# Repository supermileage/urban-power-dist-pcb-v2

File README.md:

# urban-power-dist-pcb-v2

Meet *Shuriken*! Replacement for the old urban low power distribution PCB, [*Spidey*](https://github.com/supermileage/urban-power-dist-pcb).

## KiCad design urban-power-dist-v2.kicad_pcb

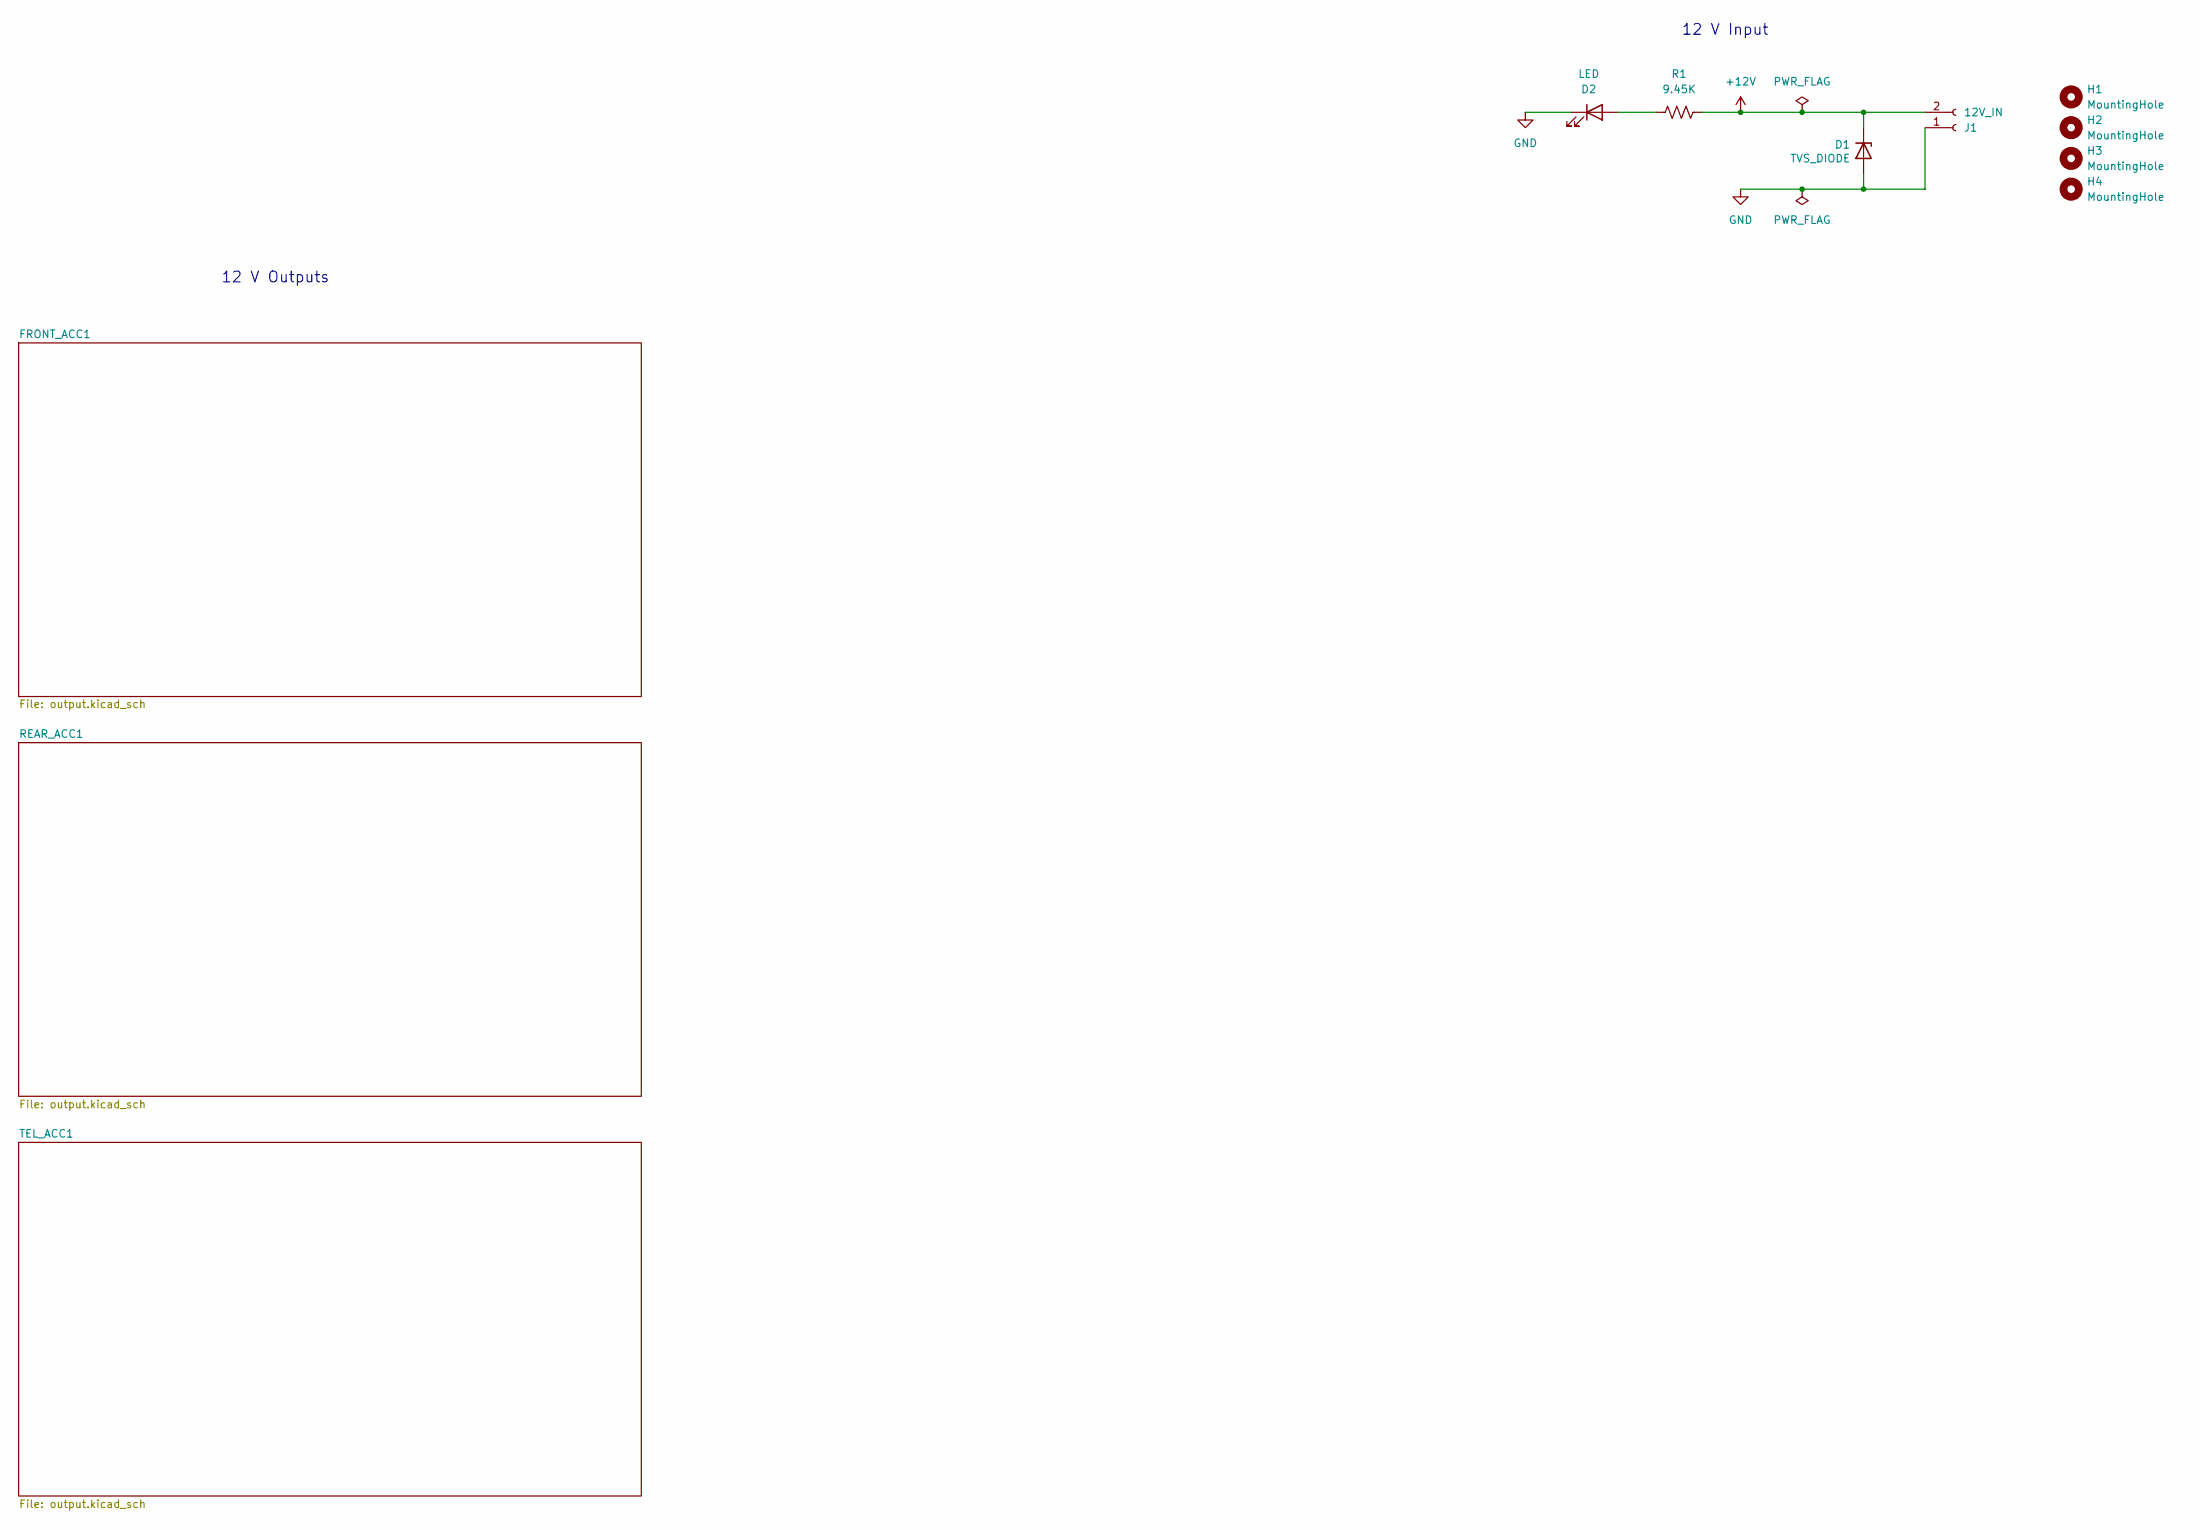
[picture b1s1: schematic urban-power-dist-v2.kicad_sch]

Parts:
D1: TVS_DIODE; D_SMF
D2: LED; LED_0603_1608Metric_Pad1.05x0.95mm_HandSolder
H1, H2, H3, H4: MountingHole; MountingHole_3.2mm_M3
J1: 12V_IN; ATF132PBM03
R1: 9.45K; R_1206_3216Metric_Pad1.30x1.75mm_HandSolder

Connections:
+12V: D1.1 (K), J1.2, R1.1; also elsewhere on the board
GND: D1.2 (A), D2.1 (K), J1.1; also elsewhere on the board
unnamed: D2.2 (A), R1.2

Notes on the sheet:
12 V Outputs
12 V Input

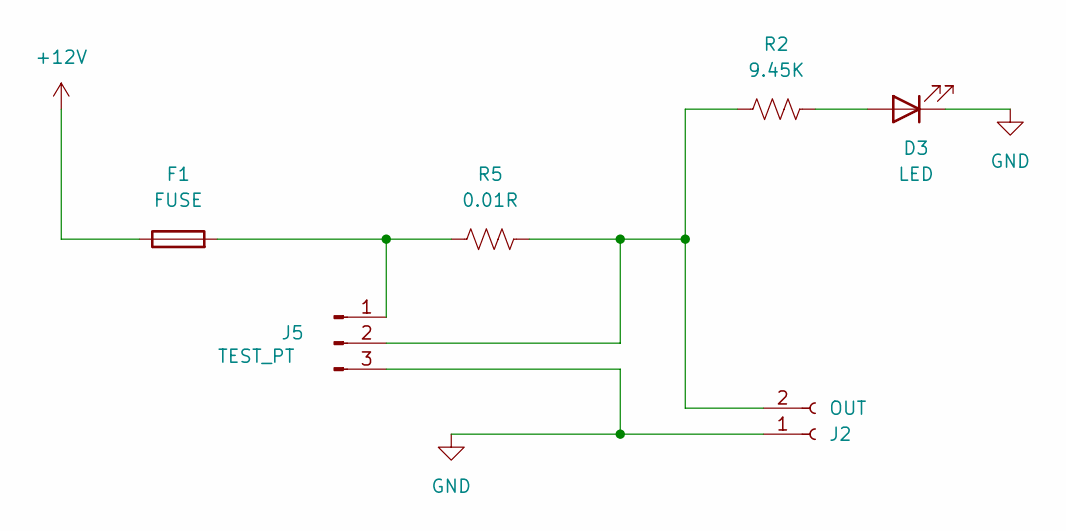
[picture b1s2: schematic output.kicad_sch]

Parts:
D3: LED; LED_0603_1608Metric_Pad1.05x0.95mm_HandSolder
F1: FUSE; Fuseholder_Blade_Mini_Keystone_3568
J2: OUT; ATF132PBM03
J5: TEST_PT; PinHeader_1x03_P2.54mm_Vertical
R2: 9.45K; R_1206_3216Metric_Pad1.30x1.75mm_HandSolder
R5: 0.01R; R_0805_2012Metric_Pad1.20x1.40mm_HandSolder

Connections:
+12V: F1.1; also elsewhere on the board
GND: D3.1 (K), J2.1, J5.3; also elsewhere on the board
unnamed: D3.2 (A), R2.1
unnamed: J2.2, J5.2, R2.2, R5.2
unnamed: F1.2, J5.1, R5.1

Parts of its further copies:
D4, D5: LED; LED_0603_1608Metric_Pad1.05x0.95mm_HandSolder
F2, F3: FUSE; Fuseholder_Blade_Mini_Keystone_3568
J3, J4: OUT; ATF132PBM03
J6, J7: TEST_PT; PinHeader_1x03_P2.54mm_Vertical
R3, R4: 9.45K; R_1206_3216Metric_Pad1.30x1.75mm_HandSolder
R6, R7: 0.01R; R_0805_2012Metric_Pad1.20x1.40mm_HandSolder

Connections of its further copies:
+12V: F2.1, F3.1; also elsewhere on the board
GND: D4.1 (K), D5.1 (K), J3.1, J4.1, J6.3, J7.3; also elsewhere on the board
unnamed: D4.2 (A), R3.1
unnamed: D5.2 (A), R4.1
unnamed: J3.2, J6.2, R3.2, R6.2
unnamed: J4.2, J7.2, R4.2, R7.2
unnamed: F2.2, J6.1, R6.1
unnamed: F3.2, J7.1, R7.1

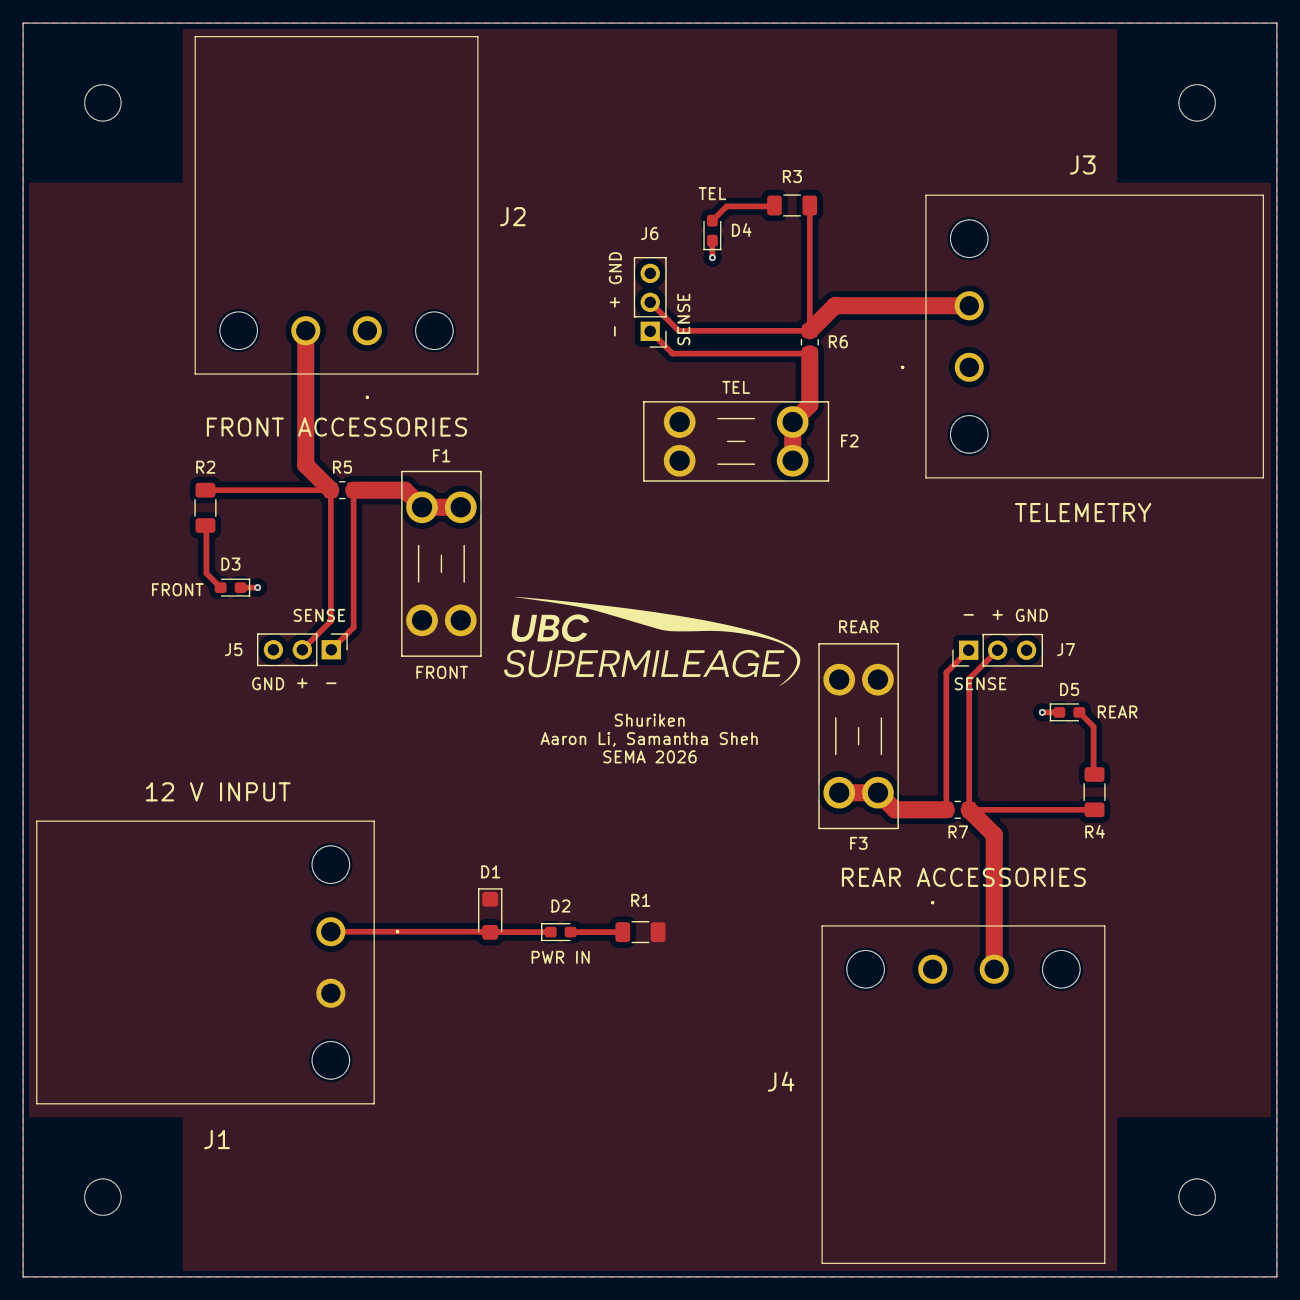
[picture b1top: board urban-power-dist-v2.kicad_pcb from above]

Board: 2 copper layers, 110.0 x 110.0 mm, 26 parts (0 on the bottom side), 12 nets.

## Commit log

2025-10-16 Finished schematic
2025-10-18 Revised schematic
2025-10-18 Revised schematic 2.0
2025-10-18 Revised schematic 3.0
2025-10-18 With hierarchical sheets
2025-10-23 pcb layout
2025-10-25 update tvs diode, layout changes
2025-10-30 layout updates
2025-10-30 close to finished layout
2025-11-01 layout DRC fixes
2025-11-02 square layout
2025-11-04 rebuild top fill
2025-11-08 final pcb edits
2025-11-09 shuriken
2025-11-09 gerbers
2026-01-01 added pcb case files
2026-05-16 readme
